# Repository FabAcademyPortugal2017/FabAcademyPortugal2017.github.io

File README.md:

# FABACADEMY WEEKLY REVIEW

* [FabAcademy Handbook](http://docs.academany.org/FabAcademy-Handbook/_book/)
* [FabAcademy Assignment and Assessments](http://docs.academany.org/FabAcademy-Assessment/_book/)

## WEEK 1 - PRINCIPLES AND PRACTICES

### Website
* [W3schools](http://www.w3schools.com)
* [Bootstrap](http://getbootstrap.com)
* [Brackets](http://brackets.io)
* [Sublime Text](https://www.sublimetext.com)
* [MarkDown](https://daringfireball.net/projects/markdown)

### Project Management
* [Google Calendar](https://calendar.google.com/)
* [embbed Google Calendar](https://support.google.com/calendar/answer/41207?hl=en)
* [GanttChart](http://www.ganttproject.biz/) > Create tasks and milestones. Aside from the start date and duration, every task may have priority, cost, color and fill pattern, text notes and user-defined custom fields. 
* [GanttView](https://github.com/thegrubbsian/jquery.ganttView) > The jQuery.ganttView plugin is a very lightweight plugin for creating a Gantt chart in plain HTML...no vector graphics or images required. The plugin supports dragging and resizing the Gantt blocks and callbacks to trap the updated data.

### GIT
* [git github](http://humansthatmake.com/github/)

### Final Project Ideas
* [Project development week](http://academy.cba.mit.edu/classes/project_development/index.html)
* [Last Year Students](http://archive.fabacademy.org/archives/2016/master/students.html)
* [MIT HTMAA student pages](http://fab.cba.mit.edu) > click under classes to see the full list of courses and years.

### Image sizes
* [adding images html](http://www.w3schools.com/html/html_images.asp) > UPLOAD ALL IMAGES TO THE LOCAL REPO!!! DON'T USE THIRD PARTY SERVICES LIKE FLICKR
* maximum recommended image size: 800x600px
* prefered image format: .png

## WEEK 2 - COMPUTER AIDED DESIGN

### 2D Design
* [bitmap vs vector](https://www.youtube.com/watch?v=fy9Pby0Gzsc)
* [Gimp](https://www.gimp.org/)
* [Inkscape](https://inkscape.org/en/)

### 3D Modeling
* [mesh vs nurbs](https://www.youtube.com/watch?v=Lm1G5jJ6JC8)
* [Blender](https://www.blender.org/)
* [Rhinoceros 3D](https://www.rhino3d.com/)
* [FreeCad](https://www.freecadweb.org/)
* [SolidWorks](http://www.solidworks.com/) > for getting the free maker license please get in touch with your instructor (Luís Carvão)
* [Fusion360](http://www.autodesk.com/products/fusion-360/overview) > for getting the free maker license please get in touch with your instructor (Luís Carvão)

### Animation Upload
* [html5 embed video](http://www.w3schools.com/html/html5_video.asp) > UPLOAD ALL VIDEOS TO THE LOCAL REPO!!! DON'T USE THIRD PARTY SERVICES LIKE YOUTUBE
* maximum recommended video size: 600x400px
* prefered video format/codec: H.264/MPEG-4 AVC
* [VLC](http://www.videolan.org/vlc/index.html) > For video compression go to: Multimedia>Convert/Save

## WEEK 3 - COMPUTER CONTROLLED CUTTING
* [Kenny Cheung aka The Nasa Guy](https://dspace.mit.edu/handle/1721.1/78199#files-area)
* [press-fit construction kit](https://www.google.pt/search?safe=off&client=ubuntu&hs=9lt&channel=fs&biw=1215&bih=897&tbm=isch&sa=1&q=modular+structures+lasercut&oq=modular+structures+lasercut&gs_l=img.3...5912.11623.0.11794.0.0.0.0.0.0.0.0..0.0....0...1c.1.64.img..0.0.0.hgyfOWT_l2A#safe=off&channel=fs&tbm=isch&q=press+fit+construction+kit)
* parametric 2D softwares: Inkscape, Antimony, [Matter Machine](http://mattermachine.com/), Grasshopper, Freecad, SolidWorks, Onshape...
* [what not to do for this week](http://fabacademy.org/archives/2014/students/cosme.vasco/img/week3/restos.jpg) > please make a small test cut first so you can check tolerances
* Glue is a sign of failure.

## WEEK 4 - ELECTRONICS PRODUCTION
* [fabmodules](fabmodules.org)
* [prepare Modela for machining circuits](http://www.youtube.com/watch?v=XdamEhs2RIk&list=PL-xEsC0ZUCUM42QNHaOOdoOwYg0j251dU&index=1)
* [why FR1/FR2 copper board?](http://www.youtube.com/watch?v=XdamEhs2RIk&list=PL-xEsC0ZUCUM42QNHaOOdoOwYg0j251dU&index=1)
* [ISP that doesn't require Crystal/Resonator](http://fab.cba.mit.edu/classes/863.16/doc/projects/ftsmin/index.html)
* [How to solder smd components](http://makezine.com/2016/02/19/learn-simple-surface-mount-soldering-in-collins-lab/)
* [ISP interface explained](https://learn.sparkfun.com/tutorials/serial-peripheral-interface-spi)
* [other programming methods](http://fabacademy.org/archives/2015/eu/students/gunnarsson.thorarinn_b.b/docs/d7/ProgrammingMethods.pdf)

## WEEK 5 - 3D SCANNING AND PRINTING
* [Meshlab scan alignment for a multiple part scan](https://www.youtube.com/watch?v=4g9Hap4rX0k)
* [Meshlab merge scans with poisson reconstruction](https://www.youtube.com/watch?v=dTkiPsNZg_o)
* [MeshMixer hollow models for Formlabs](https://formlabs.com/blog/how-to-hollow-out-3d-models/)
* [Rhino mesh repair tools](https://design.umn.edu/current_students/leo/hall/documents/Rhino_STL_repair.pdf)
* [common FDM 3d printing issues](http://support.3dverkstan.se/article/23-a-visual-ultimaker-troubleshooting-guide)

## WEEK 6 - ELECTRONICS DESIGN
* [Arduino led and button project](https://www.arduino.cc/en/tutorial/button)
* [read the Attiny 44 datasheet](http://www.atmel.com/images/doc8006.pdf)
* [What is a pull-up resistor and why do we need to use it with a button switch?](https://learn.sparkfun.com/tutorials/pull-up-resistors)
* [resistor value calculator for LED current control](http://led.linear1.org/1led.wiz)
* [Why do we need a Crystal for our microcontroller?](http://fabacademy.org/archives/2015/doc/aboutClockSpeed.html)
* [Eagle is now Autodesk Eagle!](http://www.autodesk.com/products/eagle/overview)
* [electronics design with Eagle CAD. Some differences may apply!](http://fabacademy.org/archives/2013/students/carvao.luis/week6.html)
* [Libraries for Eagle](https://github.com/FabAcademyPortugal2017/FabAcademyPortugal2017.github.io/tree/master/contents)

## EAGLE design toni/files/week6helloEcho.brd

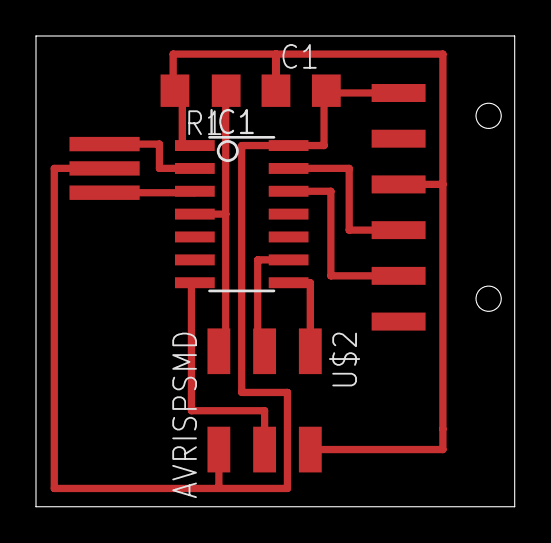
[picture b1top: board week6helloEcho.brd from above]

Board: 1 copper layer, 26.6 x 26.2 mm, 6 parts (0 on the bottom side), 10 nets.

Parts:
C1: 1uf; C1206
IC1: ATTINY44-SSU; SOIC14
JP1: 1X06-SMD
R1: 10k; R1206
U$1: RESONATOR; EFOBM
U$2: AVRISPSMD; 2X03SMD

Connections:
GND: C1.2, IC1.14, JP1.6, U$1.2, U$2.6
MISO: IC1.8, U$2.1
MOSI: IC1.7, U$2.4
unnamed: IC1.2, U$1.1
unnamed: IC1.3, U$1.3
RST: IC1.4, R1.1, U$2.5
RX: IC1.12, JP1.2
SCK: IC1.9, U$2.3
TX: IC1.13, JP1.3
VCC: C1.1, IC1.1, JP1.4, R1.2, U$2.2

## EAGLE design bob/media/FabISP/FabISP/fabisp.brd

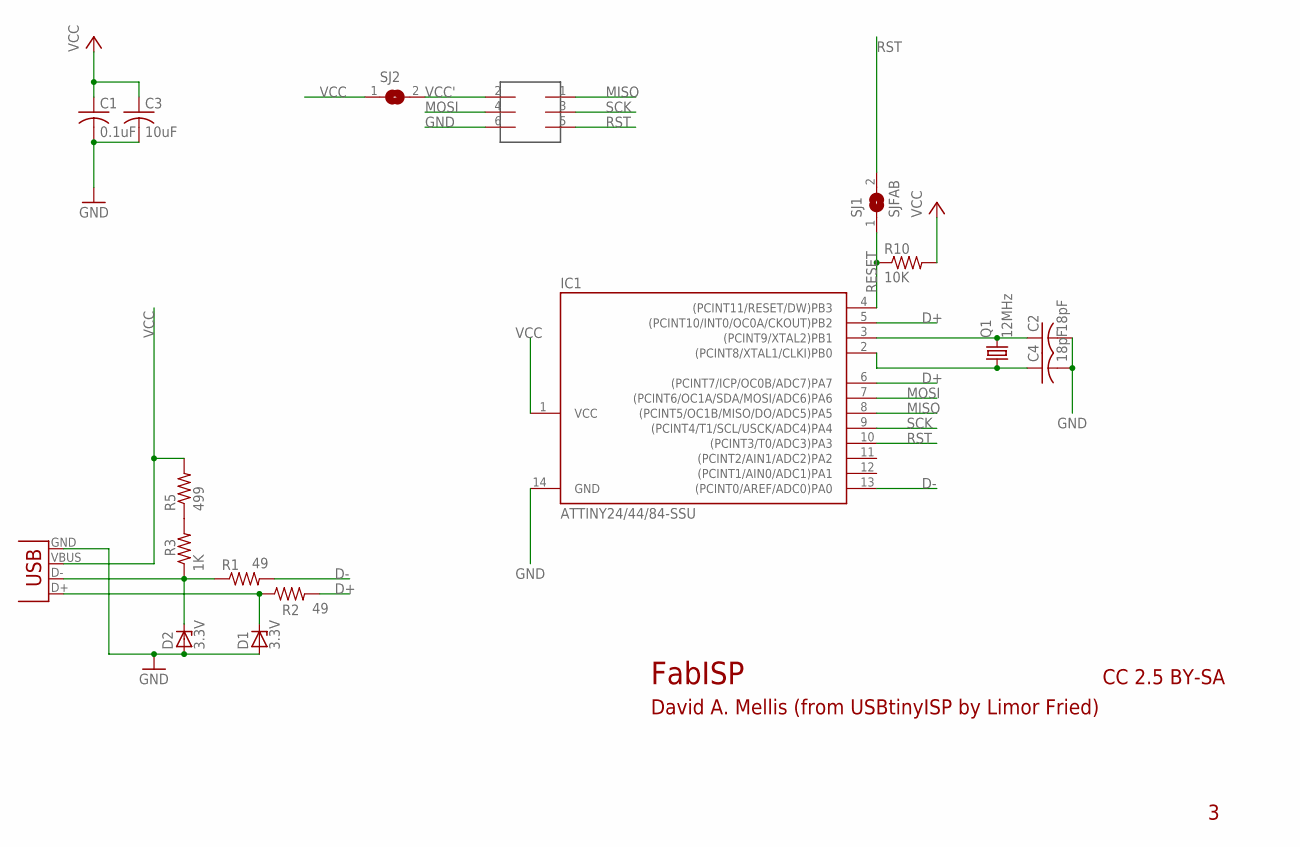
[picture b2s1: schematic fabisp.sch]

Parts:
C1: 0.1uF; C1206
C2, C4: 18pF; C1206
C3: 10uF; C1206
D1, D2: 3.3V; SOD123
IC1: ATTINY24/44/84-SSU; SOIC14
Q1: 12MHz; HC49UP
R1, R2: 49; R1206
R3: 1K; R1206
R5: 499; R1206
R10: 10K; R1206
SJ1, SJ2: SJFAB
U$1: 2X3HEADER; 2X3_SMD
X1: USB_MINIB

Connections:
D+: IC1.5 ((PCINT10/INT0/OC0A/CKOUT)PB2), IC1.6 ((PCINT7/ICP/OC0B/ADC7)PA7), R2.2
D-: IC1.13 ((PCINT0/AREF/ADC0)PA0), R1.2
GND: C1.2, C2.2, C3.2, C4.2, D1.ANODE, D2.ANODE, IC1.14 (GND), U$1.6, X1.GND
MISO: IC1.8 ((PCINT5/OC1B/MISO/DO/ADC5)PA5), U$1.1
MOSI: IC1.7 ((PCINT6/OC1A/SDA/MOSI/ADC6)PA6), U$1.4
unnamed: D2.CATHODE, R1.1, R3.1, X1.D-
unnamed: D1.CATHODE, R2.1, X1.D+
unnamed: C4.1, IC1.2 ((PCINT8/XTAL1/CLKI)PB0), Q1.1
unnamed: C2.1, IC1.3 ((PCINT9/XTAL2)PB1), Q1.2
unnamed: R3.2, R5.1
RESET: IC1.4 ((PCINT11/RESET/DW)PB3), R10.1, SJ1.1
RST: IC1.10 ((PCINT3/T0/ADC3)PA3), SJ1.2, U$1.5
SCK: IC1.9 ((PCINT4/T1/SCL/USCK/ADC4)PA4), U$1.3
VCC: C1.1, C3.1, IC1.1 (VCC), R5.2, R10.2, SJ2.1, X1.VBUS
VCC': SJ2.2, U$1.2

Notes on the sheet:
FabISP
David A. Mellis (from USBtinyISP by Limor Fried)
CC 2.5 BY-SA

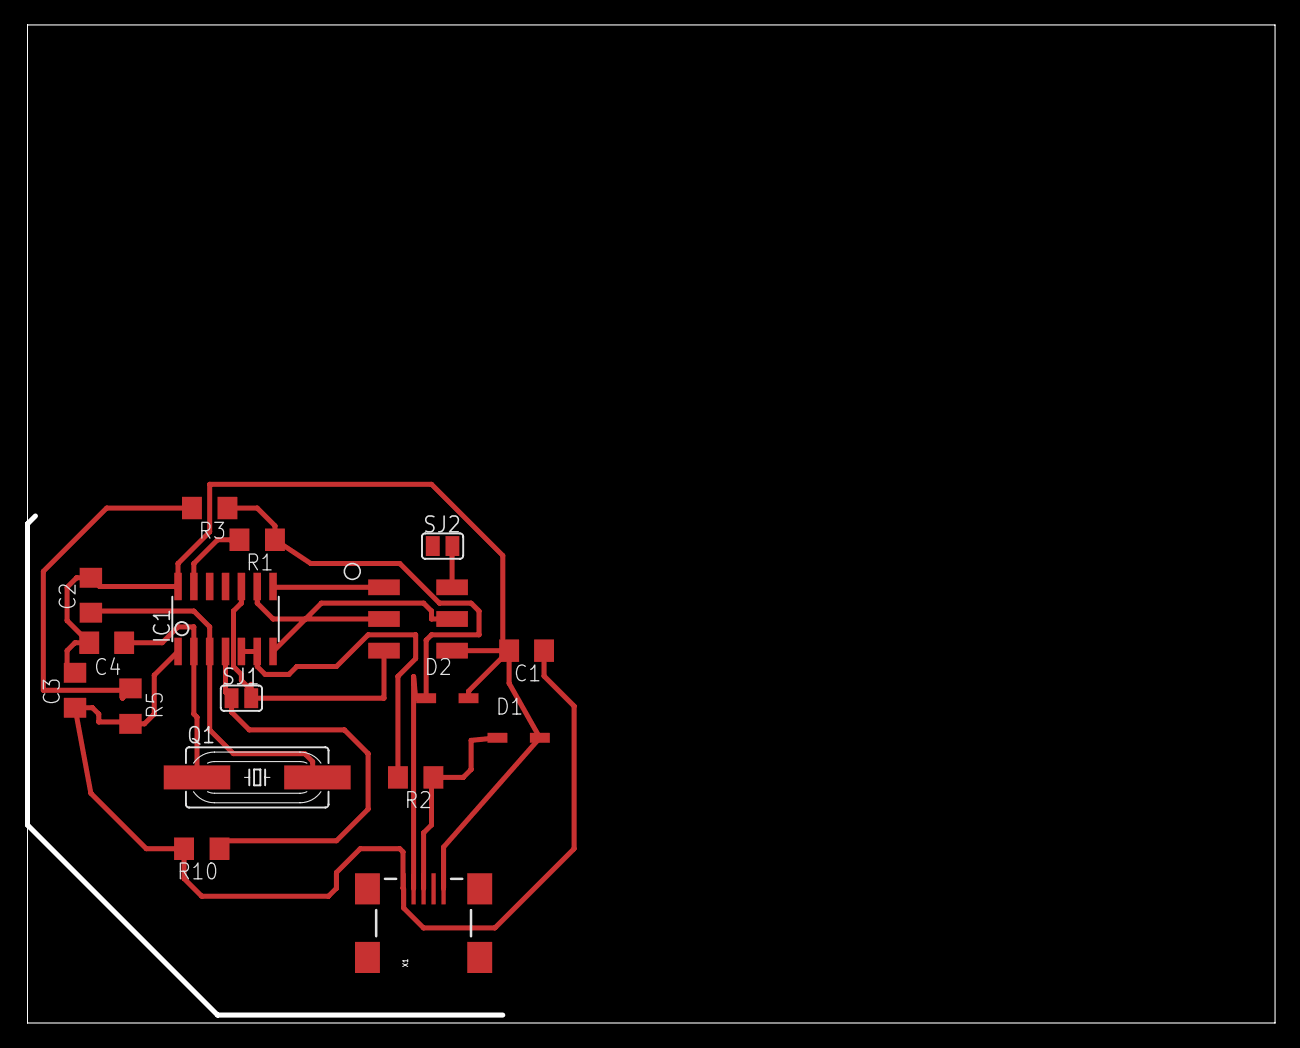
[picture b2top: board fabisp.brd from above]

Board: 2 copper layers, 100.0 x 80.0 mm, 17 parts (0 on the bottom side), 15 nets.

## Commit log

2017-01-26 first changes
2017-01-26 remake link to pic
2017-01-26 trying to get pic right
2017-01-26 argh
2017-01-26 more stuff
2017-01-26 another one
2017-01-26 creating Main Page
2017-01-26 images and etc
2017-01-27 1st task completion
2017-01-27 better first page
2017-01-27 update index FabAcademy e adição de alunos e respectivas folders
2017-01-27 minor changes
2017-01-27 index.html adicionado
2017-01-27 more comits
2017-01-27 resize image
2017-01-27 my name without accentuation
2017-01-27 commit test
2017-01-27 test
2017-01-27 deleting
2017-01-27 uploading image
2017-01-27 deleting test
2017-01-27 uploading images for project
2017-01-27 WEEK 1 REVIEW
2017-01-27 uploading pics
2017-01-27 correcting contact
2017-01-27 project
2017-01-27 updated index filipe silvestre
2017-01-27 ensaio de teste
2017-01-28 better ident and few updates
2017-01-29 teste.txt
    testando
2017-01-29 joao ribeiro
2017-01-29 change index
2017-01-29 spell check
2017-01-29 main site upload
2017-01-29 js upload
2017-01-30 removing test file
2017-01-30 adding bob and frank
2017-01-30 final project concept
2017-01-30 weeks and index
2017-01-30 Primeiro upload site filipe
2017-01-30 deleting #01 and #02
2017-01-30 deleting weekly-menu
2017-01-30 new site version upload
    week1
2017-01-30 week1 update
2017-01-31 update first week
2017-01-31 gantt
2017-01-31 size images
2017-01-31 apaguei site
2017-01-31 base de trabalho Andre
2017-01-31 update gantt
2017-01-31 base code andre2
2017-01-31 small things
2017-01-31 filipa novo site
2017-01-31 deleting min css
2017-01-31 pictures size change and toni upload
2017-01-31 deleting min
2017-01-31 solving bug
2017-01-31 fix last bug
2017-01-31 Upload css
2017-02-01 Toni Barreiros site upload
2017-02-01 update antes da videconferencia de 1fev
2017-02-01 update2
2017-02-01 imagens reduzida e projeto filipa
2017-02-01 resolving conflicts
2017-02-01 updating Lucio image sizes
2017-02-01 updating Filipa navbar dropdown
2017-02-01 novo template
2017-02-01 Edited index
2017-02-01 My Webpage
2017-02-01 fist commit
2017-02-01 Made local css
2017-02-02 Start of week 2 + new fonts
2017-02-02 new background
2017-02-02 new font
2017-02-02 max with changed to 90% for better mobile compatibility
2017-02-02 image to center and 95% size
2017-02-02 just adding a br
2017-02-02 Inês site upload
    first git upload
2017-02-02 Site root update
    adding ines to menu
2017-02-02 solving firefox compatibility
2017-02-02 Page update
2017-02-02 upgrade
    some improvments on my site
2017-02-03 new page template, first upload
2017-02-03 Console Errors Fix
2017-02-03 JS repair
2017-02-03 Repair 2
2017-02-03 CSS import
2017-02-04 estrutura e primeiro design
2017-02-04 estrutura e primeiro design_1
2017-02-04 estrutura e primeiro design_3
2017-02-04 name
    name
2017-02-04 added fonts
2017-02-04 Precise Fonts
2017-02-04 Lato Add
2017-02-04 Case Sensitive
2017-02-04 Font Fix 1
2017-02-04 js move
2017-02-04 Fixed Fonts 2
2017-02-04 Page update
    added the gantt chart on week 1
    added information about me
2017-02-05 pull before push?
2017-02-06 minor changes 2
2017-02-06 minor changes 3
2017-02-06 minor changes 4
2017-02-06 Toni Week 2 upload
2017-02-06 relative links update
2017-02-06 upload link 2
2017-02-06 second update
2017-02-07 estrutura andre com 3d
2017-02-07 minor changes071
2017-02-07 ir para a cama
2017-02-07 week 1 e 2 actualizada
2017-02-07 index update
2017-02-07 WebPage upload
    2nd week assignment
2017-02-07 change
2017-02-08 third update
2017-02-08 Week2 upload
2017-02-08 Week 2 Upload Part 2
2017-02-08 week2partial1
2017-02-08 minor changesw2
2017-02-08 apaguei a animação do Toni
2017-02-08 deleting photo
2017-02-08 cleaning files
2017-02-08 second update week2
2017-02-08 render
2017-02-08 logo
2017-02-09 upload draft with video
2017-02-10 forth update
2017-02-13 laser cutting
2017-02-13 page update
    work of the week2
2017-02-14 Upload Week 3 and week 1 and 2
2017-02-14 Upload files
2017-02-14 Week3 Upload
2017-02-14 update and upload
2017-02-15 3rd week update
2017-02-15 add week3
2017-02-15 week3_1
2017-02-15 very very small bug
2017-02-15 deleting animation folder for Toni and Ines
2017-02-15 minor bug fix on index week 3 link
2017-02-15 minor bug fix image link for week3
2017-02-15 page update
    week 3 assignment
2017-02-15 final2
2017-02-15 update
    week 3
2017-02-17 Edits for week 1 and project
2017-02-21 add update
2017-02-22 4th week update - not completed
2017-02-22 JM Week 4 Update
2017-02-22 erro ortografico detetado
2017-02-22 Upload week4
2017-02-22 Upload Index
2017-02-22 New upload
2017-02-22 semana pcb
2017-02-22 page update
    New animation and week 4
2017-02-22 Error
    correcting an index error
2017-02-23 imagem grande
2017-02-23 alteraçõe.
2017-02-24 recent edits
2017-02-25 Path error fix
2017-02-27 added files
2017-02-28 page update
    week5
2017-03-01 Assignment of week 5 upload
2017-03-01 update index
2017-03-01 5th week update
2017-03-01 5th week update-problem with extensions on images
2017-03-01 semana3D
2017-03-01 Upload
2017-03-01 partial week 4
2017-03-01 alterações tamanhos de imagens e zip de ficheiros 3d
2017-03-01 still partial but better
2017-03-01 done
2017-03-01 add video and edit chart
2017-03-02 3d print and scan update with photos
2017-03-02 update 3d
2017-03-02 Loop in gif file
2017-03-02 updates to the html code and file location
2017-03-02 3dprint actualizado
2017-03-02 updates moving things optimizing
2017-03-02 estrutura
2017-03-02 correcting codes aligning video
2017-03-02 centralise table
2017-03-05 uploading EagleCad libraries
2017-03-05 preview week6
2017-03-05 added video
2017-03-05 correcting video path
2017-03-06 update link
2017-03-06 fix links
2017-03-06 broken link
2017-03-06 trying to fix broken video
2017-03-06 just work already!
2017-03-06 out of ideas
2017-03-06 a test
2017-03-06 test 2
2017-03-07 Week 6 update
2017-03-07 final 3d printing test photos
2017-03-07 title update
2017-03-08 6th week
2017-03-08 Upload week 6
    Actualização de restantes paginas
2017-03-08 going to sleep
2017-03-08 updating image sizes
2017-03-08 more updates I think its ready
2017-03-08 video fix trial
2017-03-08 nao deveria ser tao difícil assim, tirei o audio desta vez
2017-03-08 hard stuff my video just doesn't load.
2017-03-08 looks better ?
2017-03-08 brute force
2017-03-08 deleting extra videos
2017-03-08 fix stuff
2017-03-08 small update
2017-03-08 page update
    week6
2017-03-08 correction
    image correction
2017-03-08 correction2
    index correction
2017-03-08 semana6
2017-03-08 EDITS
2017-03-08 update the weeks
2017-03-09 electronicsdesign1
2017-03-13 first commit to week7
2017-03-14 7th week
2017-03-15 Upload week7
2017-03-15 update week 7
2017-03-15 minor week7 link change
2017-03-30 Update week 9
2017-03-30 photo update
2017-03-31 semana 9
2017-03-31 pequenas alteracoes
2017-04-04 Page Update
    work update
2017-04-04 actualização
2017-04-19 small changes
2017-04-19 machine building
2017-04-19 missing link
2017-04-19 Week 11 Upload
2017-04-19 WEEK 10 ERRO
2017-05-02 week 13 update
    finished
2017-05-02 links update
2017-06-20 sync com fab aca
2017-06-25 w3Andre
2017-06-29 ines update
2025-07-22 Update Lucio's content to 2020 FabAcademy documentation
